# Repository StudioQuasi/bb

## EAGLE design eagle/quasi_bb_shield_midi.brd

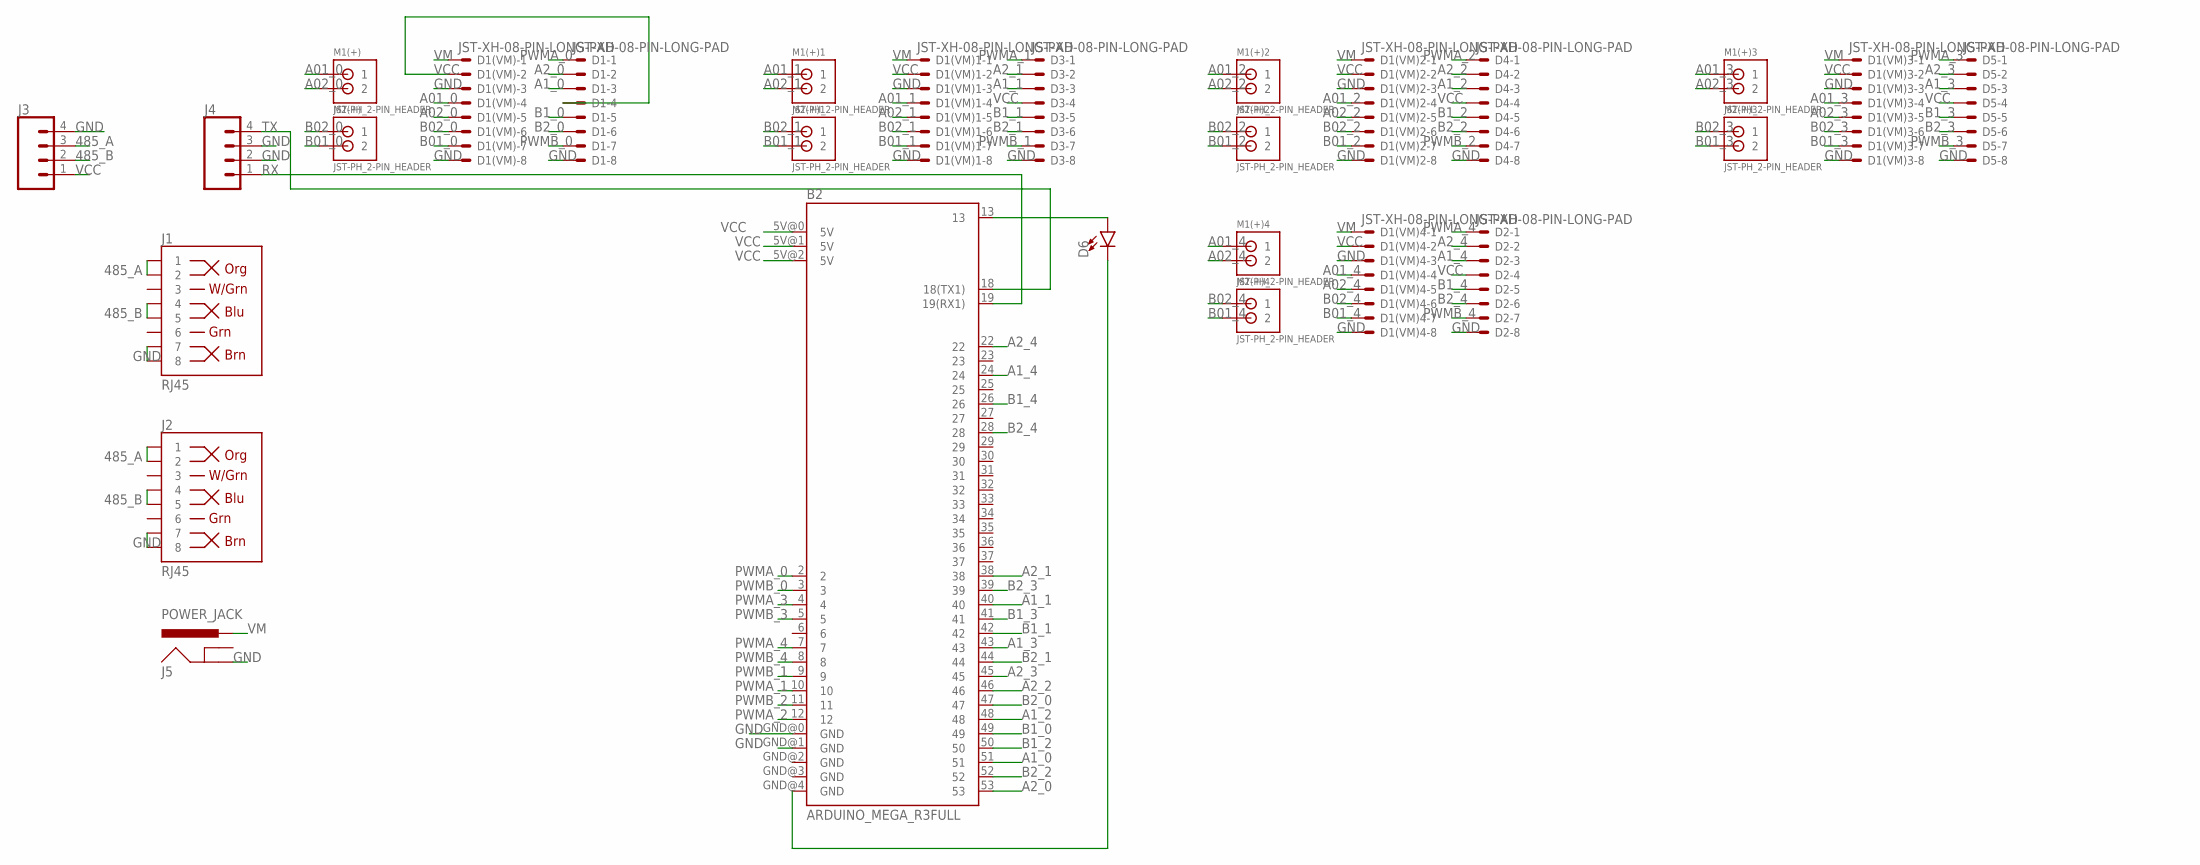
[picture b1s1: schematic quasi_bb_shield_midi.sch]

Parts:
B2: ARDUINO_MEGA_R3FULL; ARDUINO_MEGA
D1, D1(VM), D1(VM)1, D1(VM)2, D1(VM)3, D1(VM)4, D2, D3, D4, D5: JST-XH-08-PIN-LONG-PAD; JST-XH-08-PACKAGE-LONG-PAD
D6: LED-3MM-NO_SILK; LED_3MM-NS
J1, J2: RJ45; RJ45-8
J3, J4: CONN_04; 1X04
J5: POWER_JACK; POWER_JACK_PTH
M1(+), M1(+)1, M1(+)2, M1(+)3, M1(+)4, M2(+), M2(+)1, M2(+)2, M2(+)3, M2(+)4: JST-PH_2-PIN_HEADER; JST_B2B-PH_HEADER

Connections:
485_A: J1.1, J1.2, J2.1, J2.2, J3.3
485_B: J1.4, J1.5, J2.4, J2.5, J3.2
A01_0: D1(VM).4, M1(+).P1 (1)
A1_0: B2.51, D1.3
A01_1: D1(VM)1.4, M1(+)1.P1 (1)
A1_1: B2.40, D3.3
A01_2: D1(VM)2.4, M1(+)2.P1 (1)
A1_2: B2.48, D4.3
A01_3: D1(VM)3.4, M1(+)3.P1 (1)
A1_3: B2.43, D5.3
A01_4: D1(VM)4.4, M1(+)4.P1 (1)
A1_4: B2.24, D2.3
A02_0: D1(VM).5, M1(+).P2 (2)
A2_0: B2.53, D1.2
A02_1: D1(VM)1.5, M1(+)1.P2 (2)
A2_1: B2.38, D3.2
A02_2: D1(VM)2.5, M1(+)2.P2 (2)
A2_2: B2.46, D4.2
A02_3: D1(VM)3.5, M1(+)3.P2 (2)
A2_3: B2.45, D5.2
A02_4: D1(VM)4.5, M1(+)4.P2 (2)
A2_4: B2.22, D2.2
B01_0: D1(VM).7, M2(+).P2 (2)
B1_0: B2.49, D1.5
B01_1: D1(VM)1.7, M2(+)1.P2 (2)
B1_1: B2.42, D3.5
B01_2: D1(VM)2.7, M2(+)2.P2 (2)
B1_2: B2.50, D4.5
B01_3: D1(VM)3.7, M2(+)3.P2 (2)
B1_3: B2.41, D5.5
B01_4: D1(VM)4.7, M2(+)4.P2 (2)
B1_4: B2.26, D2.5
B02_0: D1(VM).6, M2(+).P1 (1)
B2_0: B2.47, D1.6
B02_1: D1(VM)1.6, M2(+)1.P1 (1)
B2_1: B2.44, D3.6
B02_2: D1(VM)2.6, M2(+)2.P1 (1)
B2_2: B2.52, D4.6
B02_3: D1(VM)3.6, M2(+)3.P1 (1)
B2_3: B2.39, D5.6
B02_4: D1(VM)4.6, M2(+)4.P1 (1)
B2_4: B2.28, D2.6
GND: B2.GND@0 (GND), B2.GND@1 (GND), D1.8, D1(VM).3, D1(VM).8, D1(VM)1.3, D1(VM)1.8, D1(VM)2.3, D1(VM)2.8, D1(VM)3.3, D1(VM)3.8, D1(VM)4.3, D1(VM)4.8, D2.8, D3.8, D4.8, D5.8, J1.7, J1.8, J2.7, J2.8, J3.4, J4.2, J4.3, J5.GND
unnamed: B2.13, D6.A
unnamed: B2.GND@4 (GND), D6.K (C)
PWMA_0: B2.2, D1.1
PWMA_1: B2.10, D3.1
PWMA_2: B2.12, D4.1
PWMA_3: B2.4, D5.1
PWMA_4: B2.7, D2.1
PWMB_0: B2.3, D1.7
PWMB_1: B2.9, D3.7
PWMB_2: B2.11, D4.7
PWMB_3: B2.5, D5.7
PWMB_4: B2.8, D2.7
RX: B2.19 (19(RX1)), J4.1
TX: B2.18 (18(TX1)), J4.4
VCC: B2.5V@0 (5V), B2.5V@1 (5V), B2.5V@2 (5V), D1.4, D1(VM).2, D1(VM)1.2, D1(VM)2.2, D1(VM)3.2, D1(VM)4.2, D2.4, D3.4, D4.4, D5.4, J3.1
VM: D1(VM).1, D1(VM)1.1, D1(VM)2.1, D1(VM)3.1, D1(VM)4.1, J5.PWR

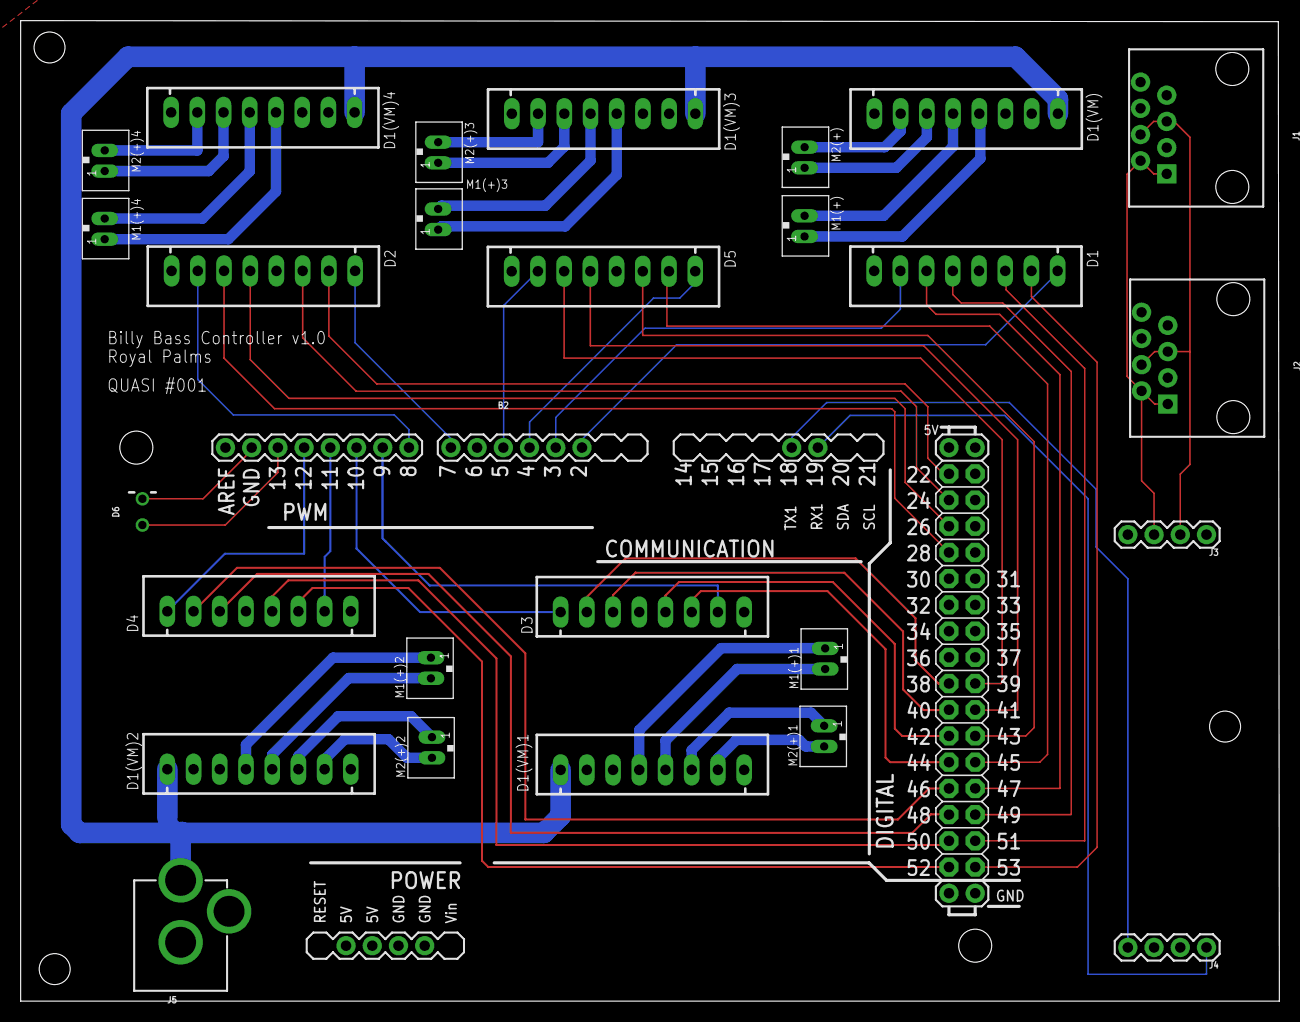
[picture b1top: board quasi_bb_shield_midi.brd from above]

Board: 2 copper layers, 122.0 x 95.0 mm, 27 parts (0 on the bottom side), 59 nets.

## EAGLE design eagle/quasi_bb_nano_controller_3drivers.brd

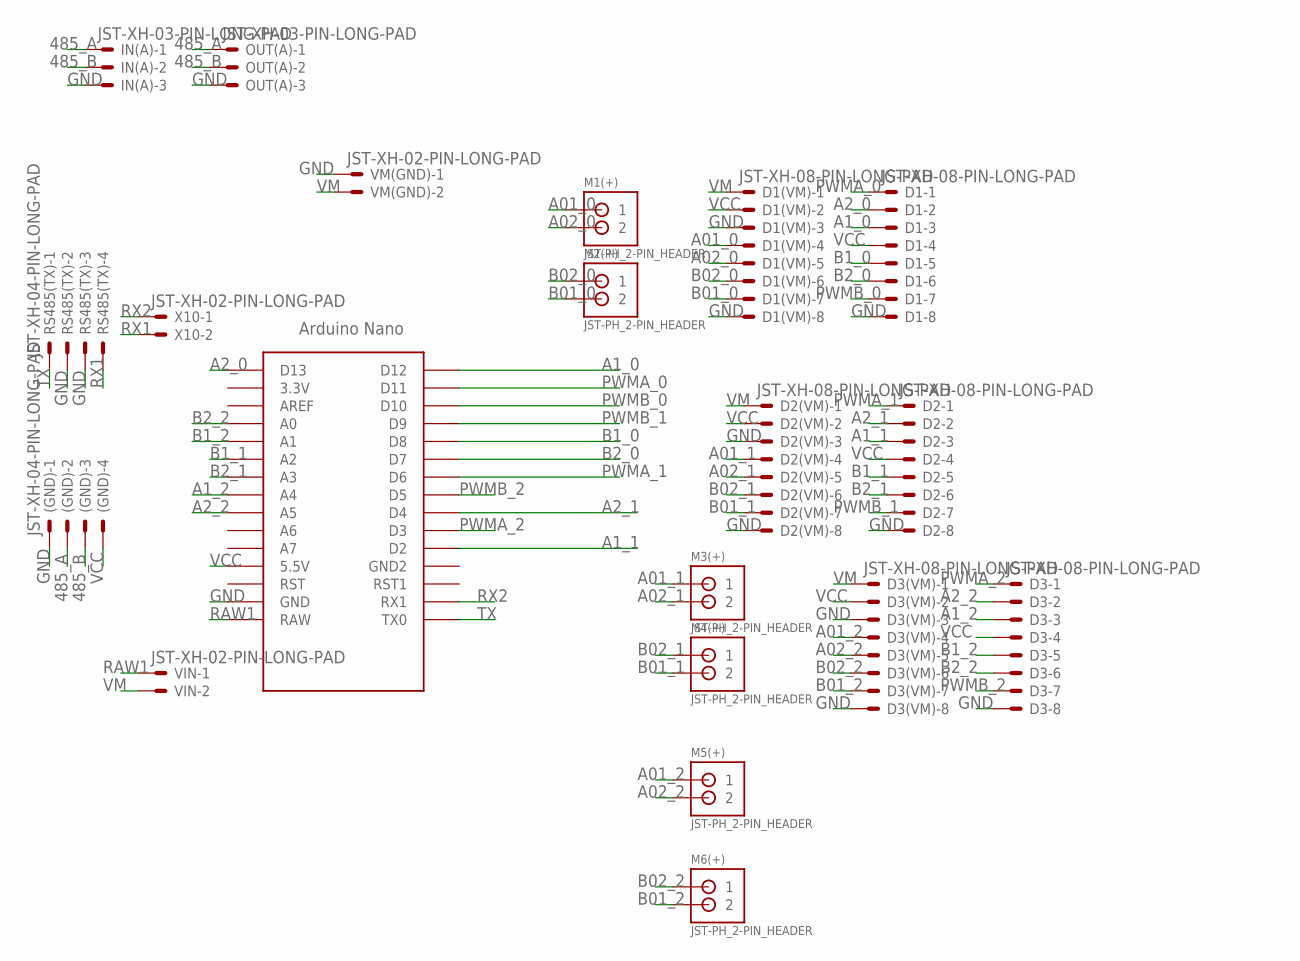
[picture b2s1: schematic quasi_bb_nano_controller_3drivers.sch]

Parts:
(GND): JST-XH-04-PIN-LONG-PAD; JST-XH-04-PACKAGE-LONG-PAD
D1, D1(VM), D2, D2(VM), D3, D3(VM): JST-XH-08-PIN-LONG-PAD; JST-XH-08-PACKAGE-LONG-PAD
IN(A): JST-XH-03-PIN-LONG-PAD; JST-XH-03-PACKAGE-LONG-PAD
M1(+), M2(+), M3(+), M4(+), M5(+), M6(+): JST-PH_2-PIN_HEADER; JST_B2B-PH_HEADER
OUT(A): JST-XH-03-PIN-LONG-PAD; JST-XH-03-PACKAGE-LONG-PAD
RS485(TX): JST-XH-04-PIN-LONG-PAD; JST-XH-04-PACKAGE-LONG-PAD
U$1: NANO
VIN: JST-XH-02-PIN-LONG-PAD; JST-XH-02-PACKAGE-LONG-PAD
VM(GND): JST-XH-02-PIN-LONG-PAD; JST-XH-02-PACKAGE-LONG-PAD
X10: JST-XH-02-PIN-LONG-PAD; JST-XH-02-PACKAGE-LONG-PAD

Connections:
485_A: (GND).2, IN(A).1, OUT(A).1
485_B: (GND).3, IN(A).2, OUT(A).2
A01_0: D1(VM).4, M1(+).P1 (1)
A1_0: D1.3, U$1.D12
A01_1: D2(VM).4, M3(+).P1 (1)
A1_1: D2.3, U$1.D2
A1_2: D3.3, U$1.A4
A01_2: D3(VM).4, M5(+).P1 (1)
A02_0: D1(VM).5, M1(+).P2 (2)
A2_0: D1.2, U$1.D13
A02_1: D2(VM).5, M3(+).P2 (2)
A2_1: D2.2, U$1.D4
A2_2: D3.2, U$1.A5
A02_2: D3(VM).5, M5(+).P2 (2)
B01_0: D1(VM).7, M2(+).P2 (2)
B1_0: D1.5, U$1.D8
B01_1: D2(VM).7, M4(+).P2 (2)
B1_1: D2.5, U$1.A2
B1_2: D3.5, U$1.A1
B01_2: D3(VM).7, M6(+).P2 (2)
B02_0: D1(VM).6, M2(+).P1 (1)
B2_0: D1.6, U$1.D7
B02_1: D2(VM).6, M4(+).P1 (1)
B2_1: D2.6, U$1.A3
B2_2: D3.6, U$1.A0
B02_2: D3(VM).6, M6(+).P1 (1)
GND: (GND).1, D1.8, D1(VM).3, D1(VM).8, D2.8, D2(VM).3, D2(VM).8, D3.8, D3(VM).3, D3(VM).8, IN(A).3, OUT(A).3, RS485(TX).2, RS485(TX).3, U$1.GND, VM(GND).1
PWMA_0: D1.1, U$1.D11
PWMA_1: D2.1, U$1.D6
PWMA_2: D3.1, U$1.D3
PWMB_0: D1.7, U$1.D10
PWMB_1: D2.7, U$1.D9
PWMB_2: D3.7, U$1.D5
RAW1: U$1.RAW, VIN.1
RX1: RS485(TX).4, X10.2
RX2: U$1.RX1, X10.1
TX: RS485(TX).1, U$1.TX0
VCC: (GND).4, D1.4, D1(VM).2, D2.4, D2(VM).2, D3.4, D3(VM).2, U$1.5V (5.5V)
VM: D1(VM).1, D2(VM).1, D3(VM).1, VIN.2, VM(GND).2

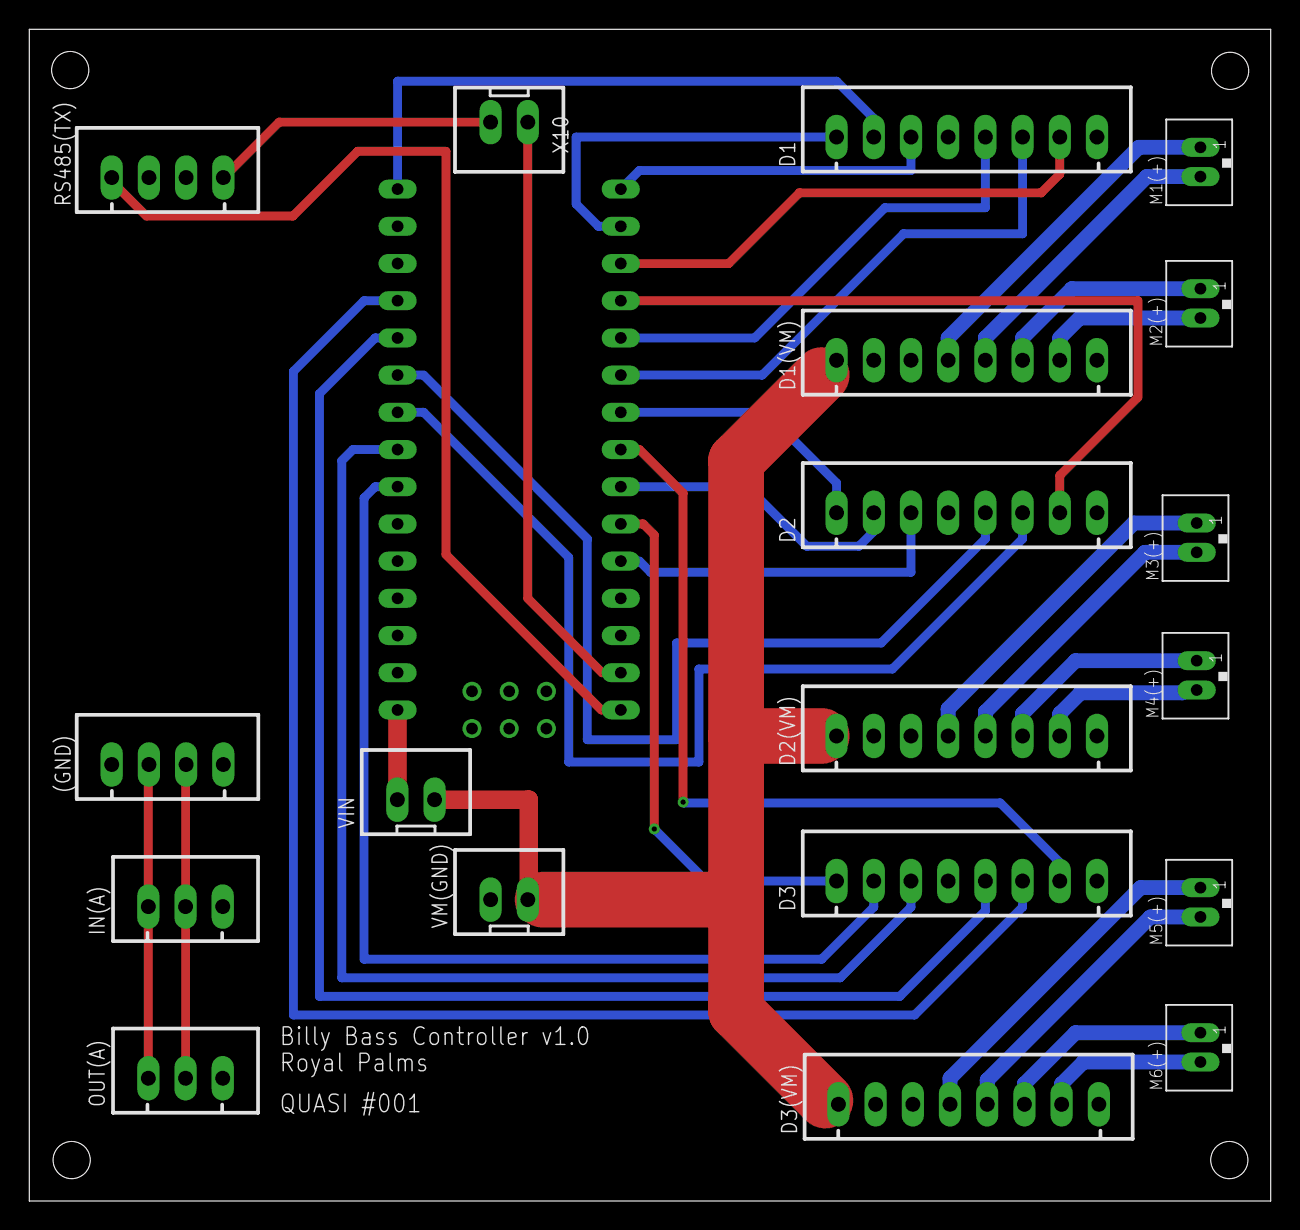
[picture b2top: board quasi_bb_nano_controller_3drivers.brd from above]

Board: 2 copper layers, 84.8 x 80.0 mm, 20 parts (0 on the bottom side), 39 nets.

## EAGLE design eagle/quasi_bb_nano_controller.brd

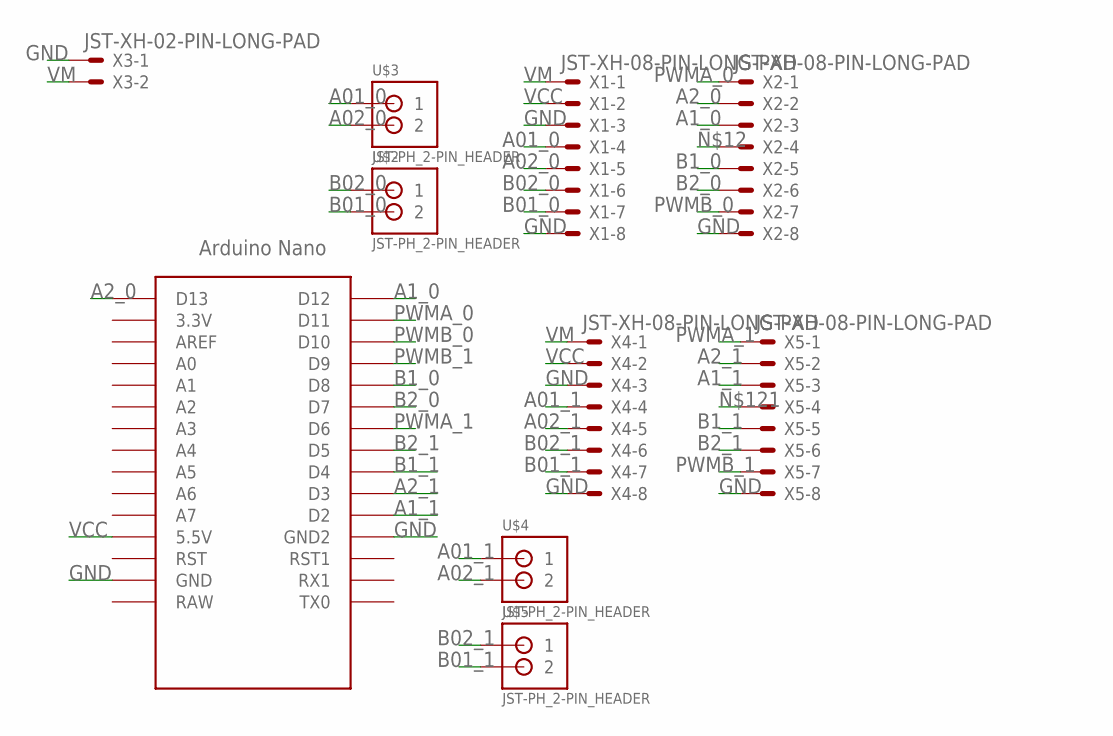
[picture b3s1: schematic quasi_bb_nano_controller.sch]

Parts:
U$1: NANO
U$2, U$3, U$4, U$5: JST-PH_2-PIN_HEADER; JST_B2B-PH_HEADER
X1, X2, X4, X5: JST-XH-08-PIN-LONG-PAD; JST-XH-08-PACKAGE-LONG-PAD
X3: JST-XH-02-PIN-LONG-PAD; JST-XH-02-PACKAGE-LONG-PAD

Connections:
A01_0: U$3.P1 (1), X1.4
A1_0: U$1.D12, X2.3
A01_1: U$4.P1 (1), X4.4
A1_1: U$1.D2, X5.3
A02_0: U$3.P2 (2), X1.5
A2_0: U$1.D13, X2.2
A02_1: U$4.P2 (2), X4.5
A2_1: U$1.D3, X5.2
B01_0: U$2.P2 (2), X1.7
B1_0: U$1.D8, X2.5
B01_1: U$5.P2 (2), X4.7
B1_1: U$1.D4, X5.5
B02_0: U$2.P1 (1), X1.6
B2_0: U$1.D7, X2.6
B02_1: U$5.P1 (1), X4.6
B2_1: U$1.D5, X5.6
GND: U$1.GND, U$1.GND1 (GND2), X1.3, X1.8, X2.8, X3.1, X4.3, X4.8, X5.8
PWMA_0: U$1.D11, X2.1
PWMA_1: U$1.D6, X5.1
PWMB_0: U$1.D10, X2.7
PWMB_1: U$1.D9, X5.7
VCC: U$1.5V (5.5V), X1.2, X4.2
VM: X1.1, X3.2, X4.1

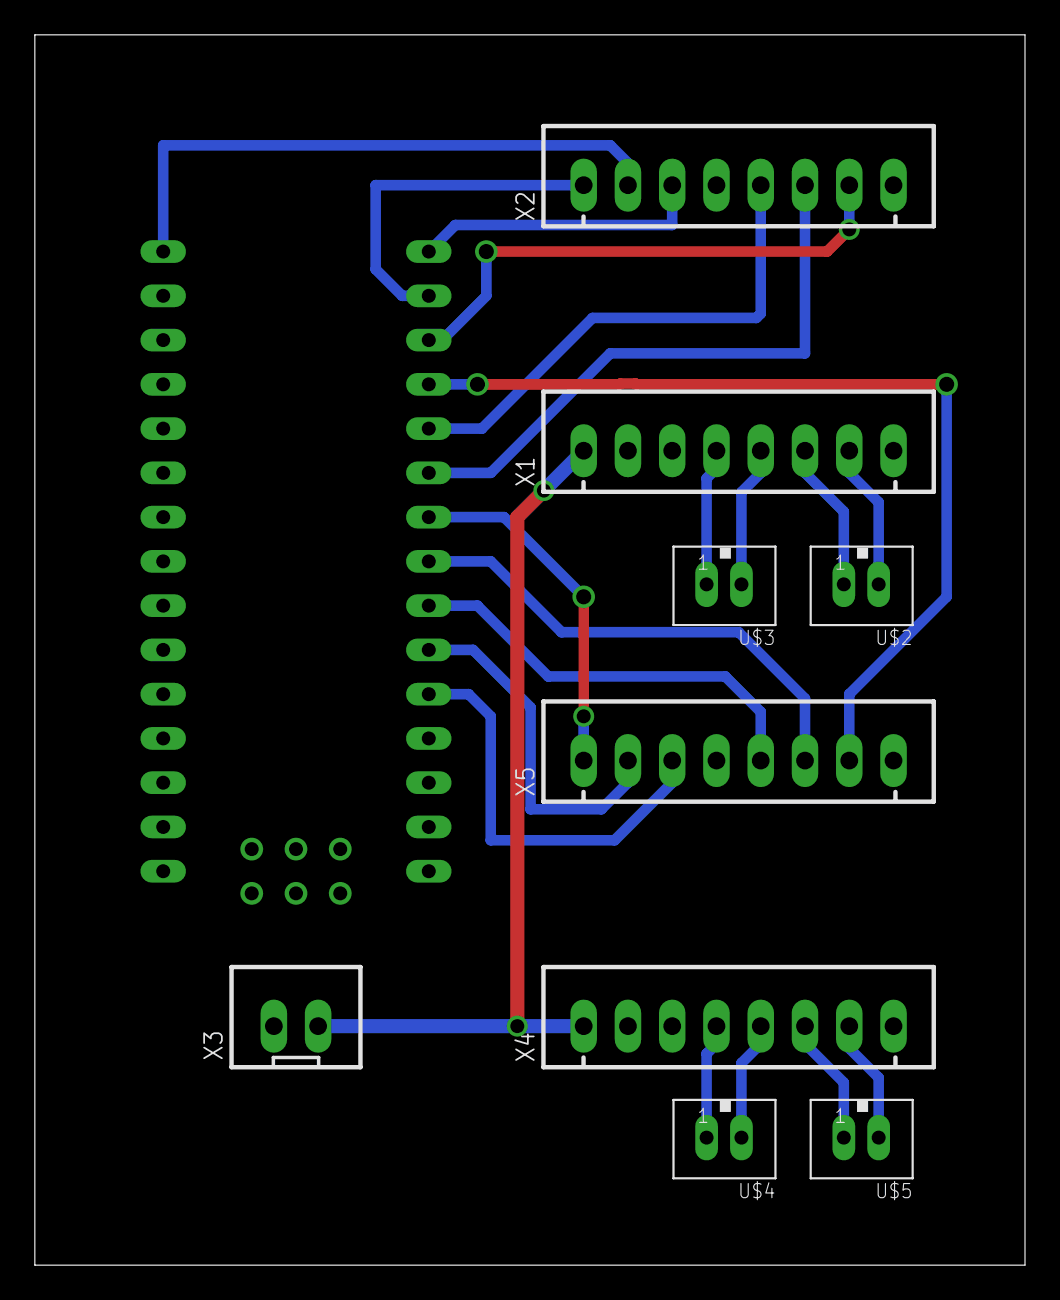
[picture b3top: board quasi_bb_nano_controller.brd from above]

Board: 2 copper layers, 56.8 x 70.6 mm, 10 parts (0 on the bottom side), 23 nets.

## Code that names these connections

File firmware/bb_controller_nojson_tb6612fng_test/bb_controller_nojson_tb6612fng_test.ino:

/* 
 *  
 * Quasi
 */

#include <Wire.h>
#include <SparkFun_TB6612.h>
#include <SoftwareSerial.h>

#define SSerialRX        A1  //Serial Receive pin
#define SSerialTX        A0  //Serial Transmit pin
#define Pin13LED         13

#include <ArduinoJson.h>

//Fix below to be array of billys
struct cmd {
  byte _cmd;
  int _time;
  bool _b1;
  bool _b2;
};

#define FORWARD 1
#define BACKWARD -1
#define RELEASE 0

#define AIN2_0 13
#define AIN1_0 12
#define PWMA_0 11

#define BIN1_0 8
#define BIN2_0 7
#define PWMB_0 10
//#define STBY_0 5

#define AIN1_1 A2
#define AIN2_1 A3
#define PWMA_1 9

#define BIN1_1 4
#define BIN2_1 2
#define PWMB_1 6
//#define STBY_1 5

#define AIN1_2 A6
#define AIN2_2 A7
#define PWMA_2 5

#define BIN1_2 A5
#define BIN2_2 A4
#define PWMB_2 3
//#define STBY_2 5


int byteReceived;
int _readIndex = 0;
byte _input[32];
byte _addr = 4;

/*

 */

const int offsetA = 1;
const int offsetB = 1;

const int STATE_LOAD_SONG = 0;
const int STATE_RUN = 1;
const int STATE_WAIT = 0;

const int CMD_OPEN = 0;
const int CMD_CLOSE = 1;
const int CMD_TAIL_ON = 2;
const int CMD_HEAD_ON = 3;
const int CMD_BODY_OFF = 4;

const int BASS_1_MOUTH  = 0;
const int BASS_1_TAIL   = 1;
const int BASS_2_MOUTH  = 2;
const int BASS_2_TAIL   = 3;
const int BASS_3_MOUTH  = 4;
const int BASS_3_TAIL   = 5;

//long mouthNext = 0;
//long bodyNext = 0;

int _low = 100;
int _high = 0;

int count = 0;
int bodyCount = 0;
int bodyPosition = 0;

int buttonState = 0;
boolean headState = false;
boolean lastHeadButton = false;

//State
int runState = 0;

//Array of commands
cmd * arrCmd;

unsigned long  _runningTime;
int   nextCmdIndex;
int   numCmd;


Motor _m0 =  Motor(AIN1_0, AIN2_0, PWMA_0, offsetA);
Motor _m1 =  Motor(BIN1_0, BIN2_0, PWMB_0, offsetA);

Motor _m2 =  Motor(AIN1_1, AIN2_1, PWMA_1, offsetA);
Motor _m3 =  Motor(BIN1_1, BIN2_1, PWMB_1, offsetA);

Motor _m4 =  Motor(A0, A1, PWMA_2, offsetA);
Motor _m5 =  Motor(BIN1_2, BIN2_2, PWMB_2, offsetA);

void setup() {
  
  Serial.begin(9600);           // set up Serial library at 9600 bps
  //Serial.println("Billy Bass Wall. Now playing: \"Sade\"");

  _m0.brake();
  _m1.brake();
  _m2.brake();
  _m3.brake();
  _m4.brake();
  _m5.brake();
  
  //pinMode(3, OUTPUT);
  //testLoop();

  driveAll(255, false);
  delay(1000);
  driveAll(0, false);
  
  runState = STATE_RUN;
}

void printDirection(int _dir)
{
  switch(_dir) {

    case FORWARD:
      Serial.print("FORWARD ");
      break;

    case BACKWARD:
      Serial.print("BACKWARD ");
      break;

    case RELEASE:
      Serial.print("RELEASE ");
      break;
  }
}

void printMotorIndex(int _index)
{
    switch(_index) {

    case BASS_1_MOUTH:
      Serial.print("BASS_1_MOUTH ");
      break;

    case BASS_1_TAIL:
      Serial.print("BASS_1_TAIL ");
      break;

    case BASS_2_MOUTH:
      Serial.print("BASS_2_MOUTH ");
      break;

    case BASS_2_TAIL:
      Serial.print("BASS_2_TAIL ");
      break;

    case BASS_3_MOUTH:
      Serial.print("BASS_3_MOUTH ");
      break;

    case BASS_3_TAIL:
      Serial.print("BASS_3_TAIL ");
      break;
  }
}

void runMotor(int _index, int _dir, int _speed)
{

  if (_dir == RELEASE)
    _speed = 0;
  else if (_dir == BACKWARD)
    _speed = -_speed;
}

void driveAll(int _val, bool _mouth) {

  if (_mouth)
  {
    if (_val == 0) {
    
    _m0.brake();
    //_m1.brake();
    _m2.brake();
    //_m3.brake();
    _m4.brake();
    //_m5.brake();
    }
    else
    {
    _m0.drive(_val);
    //_m1.drive(_val);
    _m2.drive(_val);
    //_m3.drive(_val);
    _m4.drive(_val);
    //_m5.drive(_val);
    }
  }
  else
  {
    if (_val == 0) {
    
    //_m0.brake();
    _m1.brake();
    //_m2.brake();
    _m3.brake();
    //_m4.brake();
    _m5.brake();
    }
    else
    {
    //_m0.drive(_val);
    _m1.drive(_val);
    //_m2.drive(_val);
    _m3.drive(_val);
    //_m4.drive(_val);
    _m5.drive(_val);
    }
  }



}

void testLoop() {

  _m0.drive(255);
  _m1.drive(255);
  delay(500);
  
  _m0.brake();
  _m1.brake();
  delay(500);
  
  _m0.drive(-255);
  _m1.drive(-255);
  delay(500);
  
  _m0.brake();
  _m1.brake();
  delay(500);

  _m2.drive(255);
  _m3.drive(255);
  delay(500);
  
  _m2.drive(0);
  _m3.drive(0);
  delay(500);
    
  _m2.drive(-255);
  _m3.drive(-255);
  delay(500);
  
  _m2.drive(0);
  _m3.drive(0);
  delay(500);

  Serial.println("Drive m4 and m5 to 255");
  _m4.drive(255);
  _m5.drive(255);
  delay(500);

  Serial.println("Drive m4 and m5 to 0");
  _m4.brake();
  _m5.brake();
  delay(500);

  Serial.println("Drive m4 and m5 to -255");
  _m4.drive(-255);
  _m5.drive(-255);
  delay(500);

  Serial.println("Drive m4 and m5 to 0");
  _m4.brake();
  _m5.brake();
  delay(500);

  
/*
  _m0.drive(255);
  Serial.println("Write M0");
  delay(2000);
  
  _m0.drive(-255);
  _m1.drive(255);
  Serial.println("Write M1");
  delay(2000);
  
  _m0.drive(0);
  _m1.drive(-255);
  _m2.drive(255);
  Serial.println("Write M2");
  delay(2000);
  
  _m1.drive(0);
  _m2.drive(-255);
  _m3.drive(255);
  Serial.println("Write M3");
  delay(2000);
  
  _m2.drive(0);
  _m3.drive(-255);
  _m4.drive(255);
  Serial.println("Write M4");
  delay(2000);
  
  _m3.drive(0);
  _m4.drive(-255);
  _m5.drive(255);
  Serial.println("Write M5");
  delay(2000);
  
  _m4.drive(0);
  _m5.drive(-255);
  delay(2000);
  _m5.drive(0);
 */

 //_m5.drive(255);

}


void loop() {

}

void serialEvent() {
 
  while (Serial.available()) {

    // get the new byte:
    char inChar = (char)Serial.read();

    //blink = !blink;
    //Serial.println(blink);

    switch (inChar) {

      case '1':

        Serial.println("mouth");
        driveAll(255, false);
        break;

      case '2':

        driveAll(-255, false);
        break;

      case '3':

        driveAll(0, false);
        break;

      case '4':

        Serial.println("mouth");
        driveAll(255, true);
        break;

      case '5':

        Serial.println("mouth");
        driveAll(-255, true);
        break;

      case '6':

        driveAll(0, true);
        break;
        
      case '7':

        runMotor(BASS_1_TAIL, FORWARD, 255);
        break;
        
      case '8':

        runMotor(BASS_2_TAIL, FORWARD, 255);
        break;
             
      case '9':

        runMotor(BASS_1_TAIL, RELEASE, 0); 
        break;

      case '0':

        runMotor(BASS_2_TAIL, RELEASE, 0);
        break;
    }

    if (inChar == 'a') {
      
       digitalWrite(LED_BUILTIN, HIGH);
       
    }

    if (inChar == 'b') {
      
       digitalWrite(LED_BUILTIN, LOW);
       
    }    
  }
}




  

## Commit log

2019-07-25 add arduino sketches
2019-07-25 add shield
2019-07-25 Add combined control sketch
2019-07-26 Add OF controller
2019-07-26 removed submodule
2019-07-26 Add to addons.make
2019-07-26 read and write json file
2019-07-30 Bill controller
2019-08-05 Add eagle file
2019-08-07 update board
2019-08-08 update boards
2019-08-10 Add 5 Billys
2019-08-10 Finish serial interface
2019-08-10 Update firmware
2019-08-12 Add software serial sketches
2019-08-16 add firmware
2019-08-16 Add eagle
2019-08-16 add src
2019-08-28 Many updates
2019-08-28 Control board v1.0
2019-08-29 add firmware for new control boards
2019-08-30 update the control board
2019-09-11 add pics of Billy in 6 states
2019-09-11 add smaller fish
2019-09-12 Add bass images
2019-09-12 Add the controller object and add image preview
2019-09-12 Add ofxgui params
2019-09-12 Add songs and images
2019-09-12 Add firmeware
2019-09-14 Add more gui params
2019-09-18 Add GUI
2019-09-18 Add ofxInterface
2019-09-18 merge
2019-09-20 Update admin view
2019-09-21 Add more layout params
2019-09-25 fix merge
2019-09-27 Add Arduino
2019-09-27 upload
2019-09-27 Add group IDs
2019-09-28 Fix group commands
2019-10-04 Adding more overrides for boards
2019-10-04 Add reverse motor for tail and head
2019-10-06 Add group functionality
2019-10-08 Add Shoop. Add group functionality
2019-10-09 Add tracks
2019-10-12 Add reverse for head and tail
2019-10-13 Allow multiple groups. Add soft end flap
2019-10-13 Add timeline editing
2019-10-14 Editing timeline
2019-10-16 Add firmware. Add more tracking updates
2019-10-17 Add talking heads
2019-10-17 finish once in a lifetime
2019-10-17 Latest timeline tweaks
2019-10-18 add beegees
2019-10-18 Add file
2019-10-18 add t-pain
2019-10-18 more t-pain
2019-10-19 Add chorus
2019-10-20 Add timeout to clear the fish
2019-10-21 Add songs
2019-10-22 Fix issue w/ chorus
2019-11-27 Add binary
2023-01-28 adding RAR test
2023-01-30 Fixes for song playback

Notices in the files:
parts and their libraries:
SparkFun-Connectors: Licensing: Creative Commons ShareAlike 4.0 International - https://creativecommons.org/licenses/by-sa/4.0
